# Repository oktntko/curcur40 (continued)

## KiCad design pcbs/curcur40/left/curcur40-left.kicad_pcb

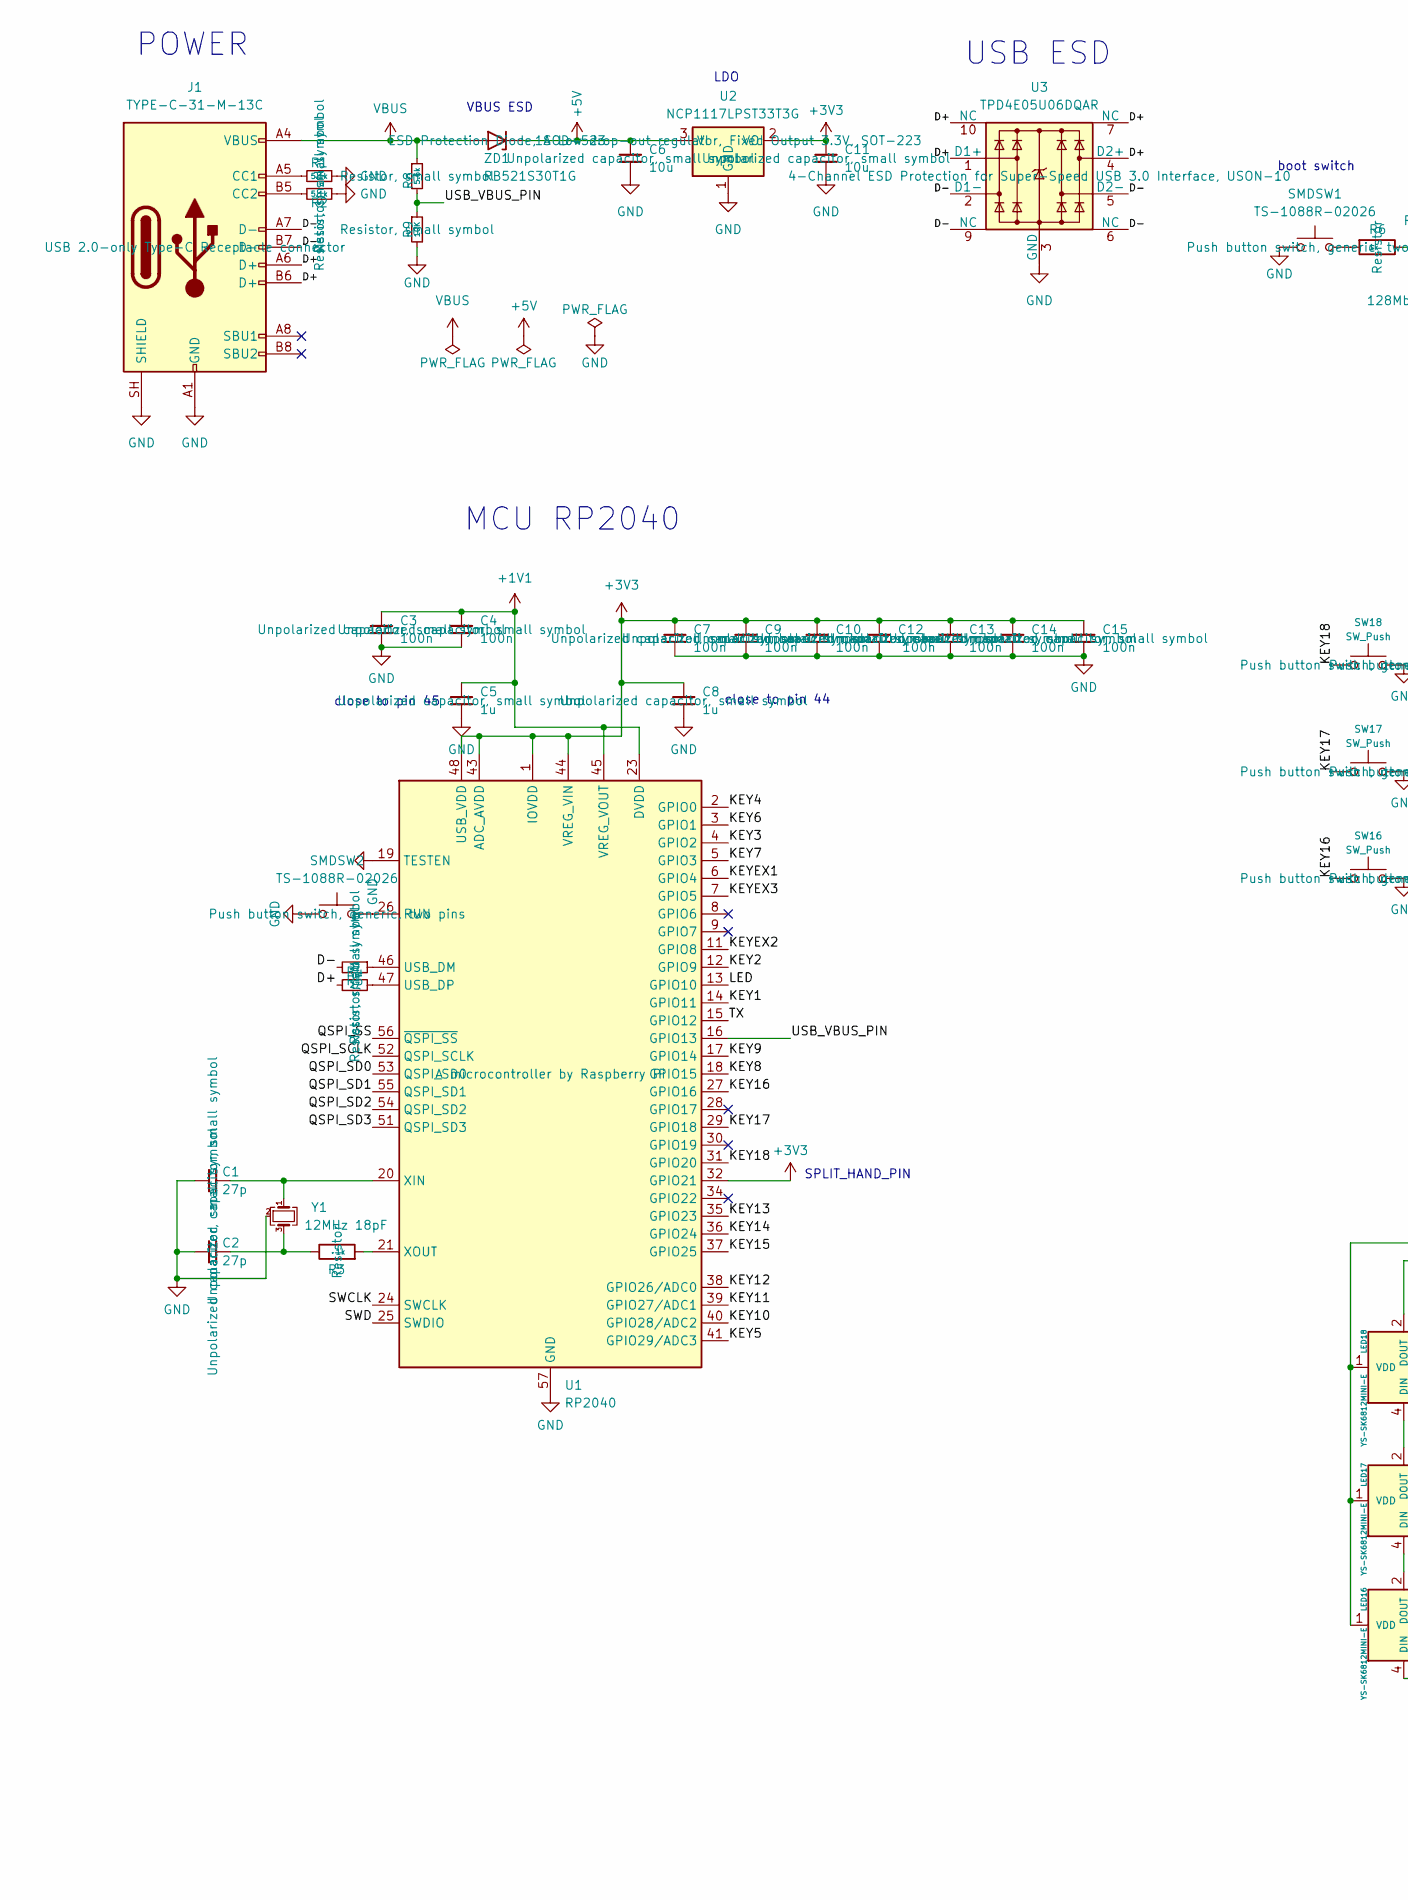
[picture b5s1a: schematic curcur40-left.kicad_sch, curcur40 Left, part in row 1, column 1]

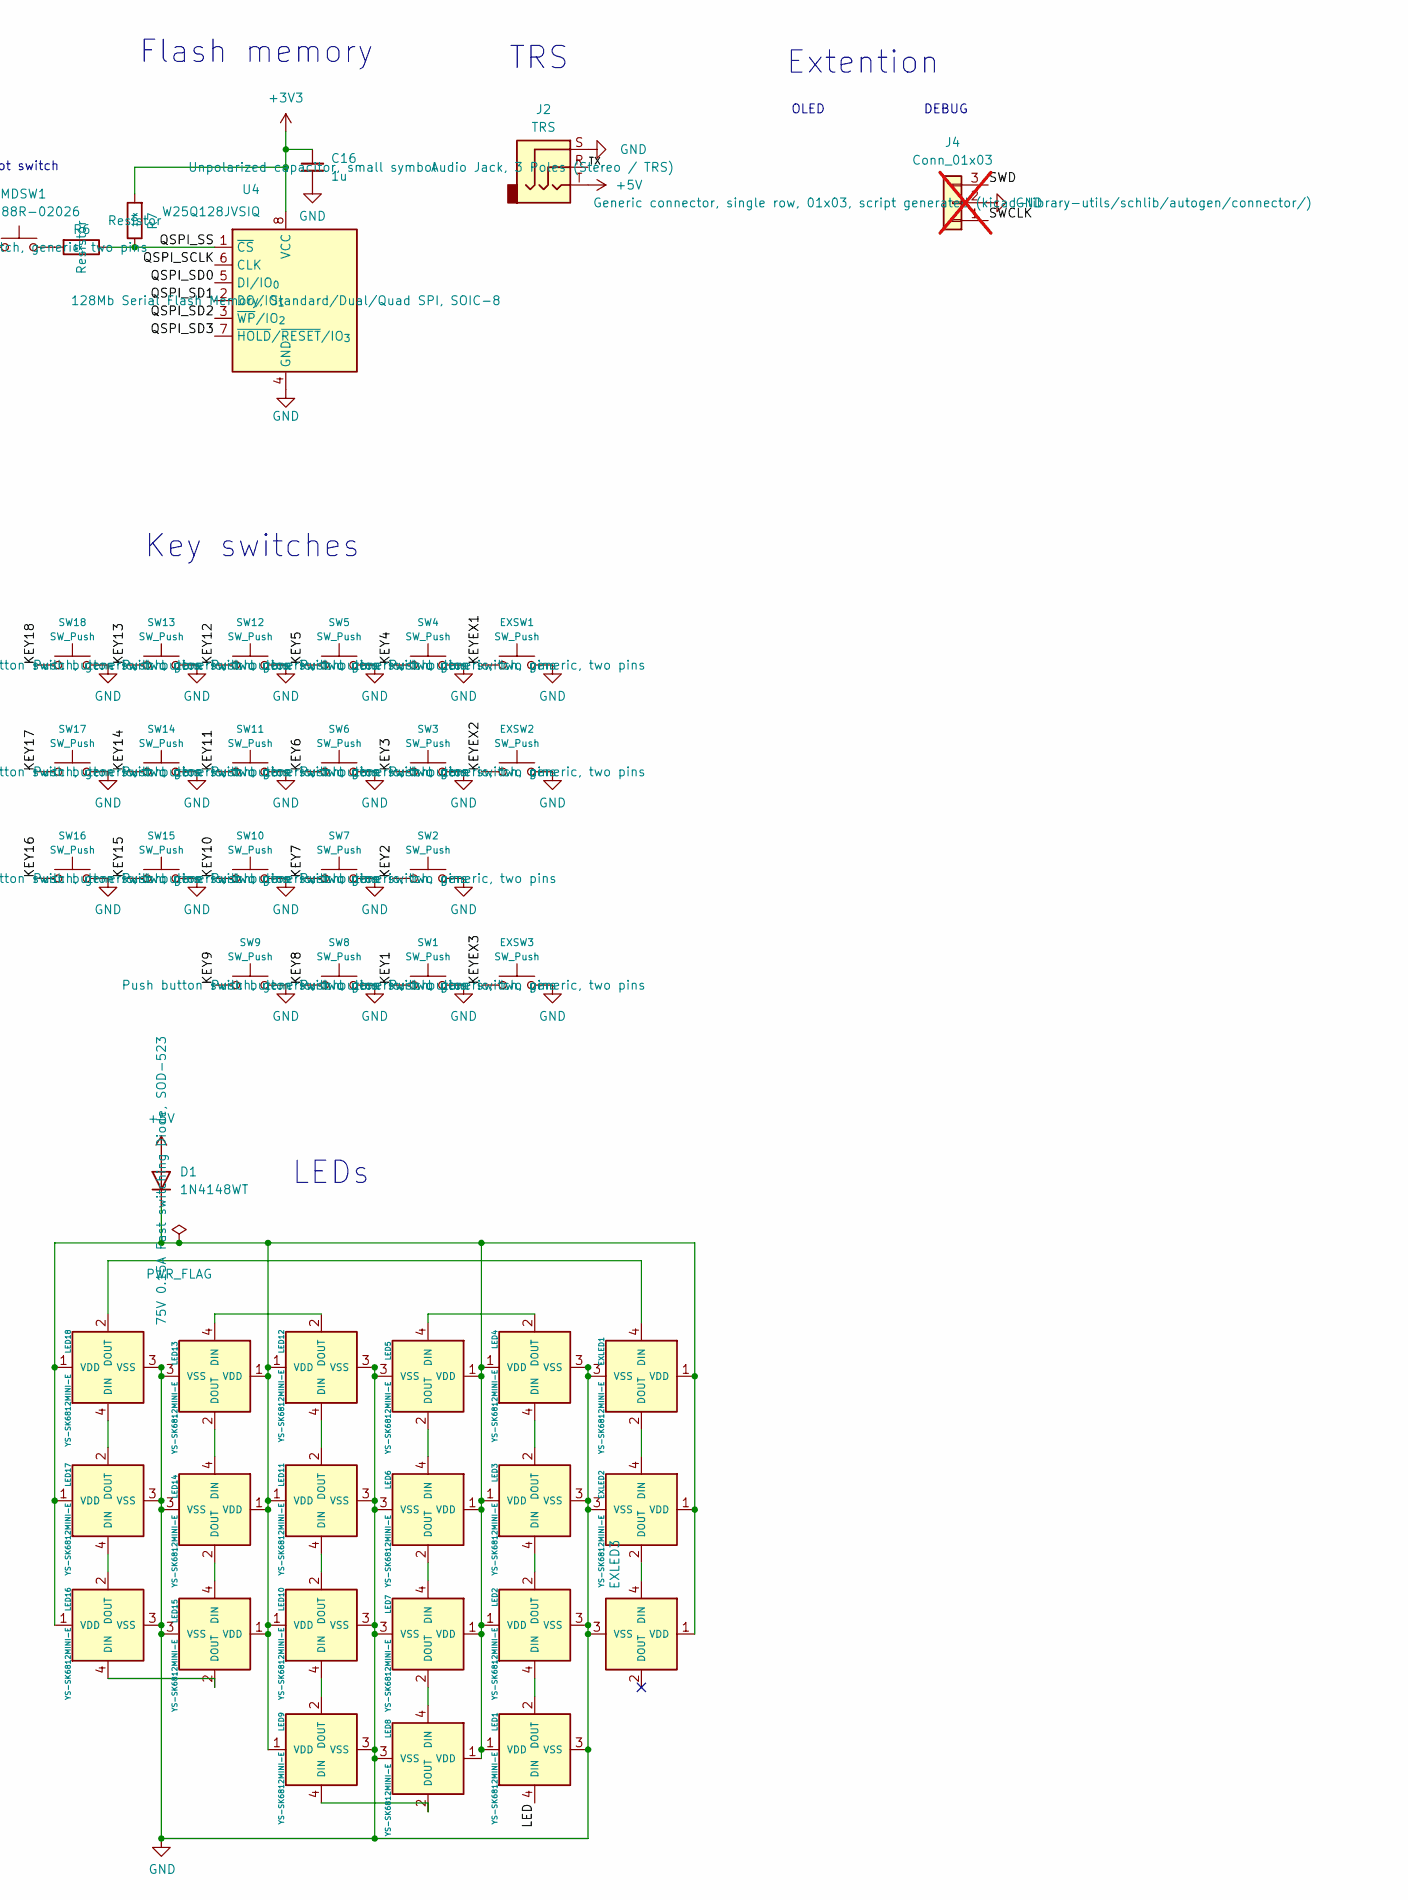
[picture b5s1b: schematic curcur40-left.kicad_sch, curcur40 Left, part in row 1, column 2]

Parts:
C1, C2: 27p; C_0402_1005Metric
C3, C4, C7, C9, C10, C12, C13, C14, C15: 100n; C_0402_1005Metric
C5, C8, C16: 1u; C_0402_1005Metric
C6, C11: 10u; C_0402_1005Metric
D1: 1N4148WT; D_SOD-523; JLCPCB Part # C232841
EXLED1, EXLED2, EXLED3: YS-SK6812MINI-E
EXSW1, EXSW2, EXSW3: SW_Push; keyswitch_choc12_hotswap_1u
J1: TYPE-C-31-M-13C; USB_C_Receptacle_TYPE-C-31-M-13C; JLCPCB Part # C2848620
J2: TRS; Jack_PJ-398A-5A_PJ-399B-6A; JLCPCB Part # C128994
J4: Conn_01x03; PinHeader_1x03_P2.54mm_Vertical; not fitted
LED1, LED2, LED3, LED4, LED5, LED6, LED7, LED8, LED9, LED10, LED11, LED12, LED13, LED14, LED15, LED16, LED17, LED18: YS-SK6812MINI-E
R1, R2: 5.1k; R_0402_1005Metric
R3, R6: 1k; R_0402_1005Metric
R4, R5: 27; R_0402_1005Metric
R7: 10k; R_0402_1005Metric
R8: 5.6k; R_0402_1005Metric
R9: 10K; R_0402_1005Metric
SMDSW1, SMDSW2: TS-1088R-02026; JLCPCB Part # C455280
SW1, SW2, SW3, SW4, SW5, SW6, SW7, SW8, SW9, SW10, SW11, SW12, SW13, SW14, SW15, SW16, SW17, SW18: SW_Push; keyswitch_choc12_hotswap_1u
U1: RP2040; QFN-56-1EP_7x7mm_P0.4mm_EP3.2x3.2mm; JLCPCB Part # C2040
U2: NCP1117LPST33T3G; SOT-223-3_TabPin2; JLCPCB Part # C146799
U3: TPD4E05U06DQAR; USON-10_2.5x1.0mm_P0.5mm; JLCPCB Part # C138714
U4: W25Q128JVSIQ; SOIC-8_5.3x5.3mm_P1.27mm; JLCPCB Part # C113767
Y1: 12MHz 18pF; Crystal_SMD_3225-4Pin_3.2x2.5mm; MFR.Part # Q22FA23V0041800; JLCPCB Part # C91749
ZD1: RB521S30T1G; D_SOD-523; JLCPCB Part # C145179

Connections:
+1V1: C3.1, C4.1, C5.1, U1.23 (DVDD), U1.45 (VREG_VOUT), U1.50 (DVDD)
+3V3: C7.1, C8.1, C9.1, C10.1, C11.1, C12.1, C13.1, C14.1, C15.1, C16.1, R7.2, U1.1 (IOVDD), U1.10 (IOVDD), U1.22 (IOVDD), U1.32 (GPIO21), U1.33 (IOVDD), U1.42 (IOVDD), U1.43 (ADC_AVDD), U1.44 (VREG_VIN), U1.48 (USB_VDD), U1.49 (IOVDD), U2.2 (VO), U4.8 (VCC)
+5V: C6.1, D1.2 (A), J2.T, U2.3 (VI), ZD1.1 (K)
/D+: J1.A6 (D+), J1.B6 (D+), R4.1, U3.1 (D1+), U3.4 (D2+), U3.7 (NC), U3.10 (NC)
/D-: J1.A7 (D-), J1.B7 (D-), R5.2, U3.2 (D1-), U3.5 (D2-), U3.6 (NC), U3.9 (NC)
/KEY1: SW1.1, U1.14 (GPIO11)
/KEY2: SW2.1, U1.12 (GPIO9)
/KEY3: SW3.1, U1.4 (GPIO2)
/KEY4: SW4.1, U1.2 (GPIO0)
/KEY5: SW5.1, U1.41 (GPIO29/ADC3)
/KEY6: SW6.1, U1.3 (GPIO1)
/KEY7: SW7.1, U1.5 (GPIO3)
/KEY8: SW8.1, U1.18 (GPIO15)
/KEY9: SW9.1, U1.17 (GPIO14)
/KEY10: SW10.1, U1.40 (GPIO28/ADC2)
/KEY11: SW11.1, U1.39 (GPIO27/ADC1)
/KEY12: SW12.1, U1.38 (GPIO26/ADC0)
/KEY13: SW13.1, U1.35 (GPIO23)
/KEY14: SW14.1, U1.36 (GPIO24)
/KEY15: SW15.1, U1.37 (GPIO25)
/KEY16: SW16.1, U1.27 (GPIO16)
/KEY17: SW17.1, U1.29 (GPIO18)
/KEY18: SW18.1, U1.31 (GPIO20)
/KEYEX1: EXSW1.1, U1.6 (GPIO4)
/KEYEX2: EXSW2.1, U1.11 (GPIO8)
/KEYEX3: EXSW3.1, U1.7 (GPIO5)
/LED: LED1.4 (DIN), U1.13 (GPIO10)
/QSPI_SCLK: U1.52 (QSPI_SCLK), U4.6 (CLK)
/QSPI_SD0: U1.53 (QSPI_SD0), U4.5 (DI/IO_{0})
/QSPI_SD1: U1.55 (QSPI_SD1), U4.2 (DO/IO_{1})
/QSPI_SD2: U1.54 (QSPI_SD2), U4.3 (~WP/IO_{2})
/QSPI_SD3: U1.51 (QSPI_SD3), U4.7 (~HOLD/~RESET/IO_{3})
/QSPI_SS: R6.1, R7.1, U1.56 (~QSPI_SS), U4.1 (~CS)
/SWCLK: J4.1, U1.24 (SWCLK)
/SWD: J4.3, U1.25 (SWDIO)
/TX: J2.R, U1.15 (GPIO12)
/USB_VBUS_PIN: R8.2, R9.1, U1.16 (GPIO13)
GND: C1.2, C2.2, C3.2, C4.2, C5.2, C6.2, C7.2, C8.2, C9.2, C10.2, C11.2, C12.2, C13.2, C14.2, C15.2, C16.2, EXLED1.3 (VSS), EXLED2.3 (VSS), EXLED3.3 (VSS), EXSW1.2, EXSW2.2, EXSW3.2, J1.A1 (GND), J1.A12 (GND), J1.B1 (GND), J1.B12 (GND), J1.SH (SHIELD), J2.S, J4.2, LED1.3 (VSS), LED2.3 (VSS), LED3.3 (VSS), LED4.3 (VSS), LED5.3 (VSS), LED6.3 (VSS), LED7.3 (VSS), LED8.3 (VSS), LED9.3 (VSS), LED10.3 (VSS), LED11.3 (VSS), LED12.3 (VSS), LED13.3 (VSS), LED14.3 (VSS), LED15.3 (VSS), LED16.3 (VSS), LED17.3 (VSS), LED18.3 (VSS), R1.1, R2.1, R9.2, SMDSW1.1, SMDSW2.1, SW1.2, SW2.2, SW3.2, SW4.2, SW5.2, SW6.2, SW7.2, SW8.2, SW9.2, SW10.2, SW11.2, SW12.2, SW13.2, SW14.2, SW15.2, SW16.2, SW17.2, SW18.2, U1.19 (TESTEN), U1.57 (GND), U2.1 (GND), U3.3 (GND), U3.8 (GND), U4.4 (GND), Y1.2 (G), Y1.4 (G)
unnamed: C2.1, R3.1, Y1.3
unnamed: D1.1 (K), EXLED1.1 (VDD), EXLED2.1 (VDD), EXLED3.1 (VDD), LED1.1 (VDD), LED2.1 (VDD), LED3.1 (VDD), LED4.1 (VDD), LED5.1 (VDD), LED6.1 (VDD), LED7.1 (VDD), LED8.1 (VDD), LED9.1 (VDD), LED10.1 (VDD), LED11.1 (VDD), LED12.1 (VDD), LED13.1 (VDD), LED14.1 (VDD), LED15.1 (VDD), LED16.1 (VDD), LED17.1 (VDD), LED18.1 (VDD)
unnamed: EXLED1.4 (DIN), LED18.2 (DOUT)
unnamed: EXLED1.2 (DOUT), EXLED2.4 (DIN)
unnamed: EXLED2.2 (DOUT), EXLED3.4 (DIN)
unnamed: J1.A5 (CC1), R1.2
unnamed: J1.B5 (CC2), R2.2
unnamed: LED1.2 (DOUT), LED2.4 (DIN)
unnamed: LED2.2 (DOUT), LED3.4 (DIN)
unnamed: LED3.2 (DOUT), LED4.4 (DIN)
unnamed: LED4.2 (DOUT), LED5.4 (DIN)
unnamed: LED5.2 (DOUT), LED6.4 (DIN)
unnamed: LED6.2 (DOUT), LED7.4 (DIN)
unnamed: LED7.2 (DOUT), LED8.4 (DIN)
unnamed: LED8.2 (DOUT), LED9.4 (DIN)
unnamed: LED9.2 (DOUT), LED10.4 (DIN)
unnamed: LED10.2 (DOUT), LED11.4 (DIN)
unnamed: LED11.2 (DOUT), LED12.4 (DIN)
unnamed: LED12.2 (DOUT), LED13.4 (DIN)
unnamed: LED13.2 (DOUT), LED14.4 (DIN)
unnamed: LED14.2 (DOUT), LED15.4 (DIN)
unnamed: LED15.2 (DOUT), LED16.4 (DIN)
unnamed: LED16.2 (DOUT), LED17.4 (DIN)
unnamed: LED17.2 (DOUT), LED18.4 (DIN)
unnamed: R6.2, SMDSW1.2
unnamed: SMDSW2.2, U1.26 (RUN)
unnamed: R5.1, U1.46 (USB_DM)
unnamed: R4.2, U1.47 (USB_DP)
unnamed: C1.1, U1.20 (XIN), Y1.1
unnamed: R3.2, U1.21 (XOUT)
VBUS: J1.A4 (VBUS), J1.A9 (VBUS), J1.B4 (VBUS), J1.B9 (VBUS), R8.1, ZD1.2 (A)

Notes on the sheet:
MCU RP2040
Key switches
OLED
close to pin 45
DEBUG
USB ESD
LDO
Flash memory
POWER
LEDs
Extention
TRS
VBUS ESD
SPLIT_HAND_PIN
boot switch
close to pin 44

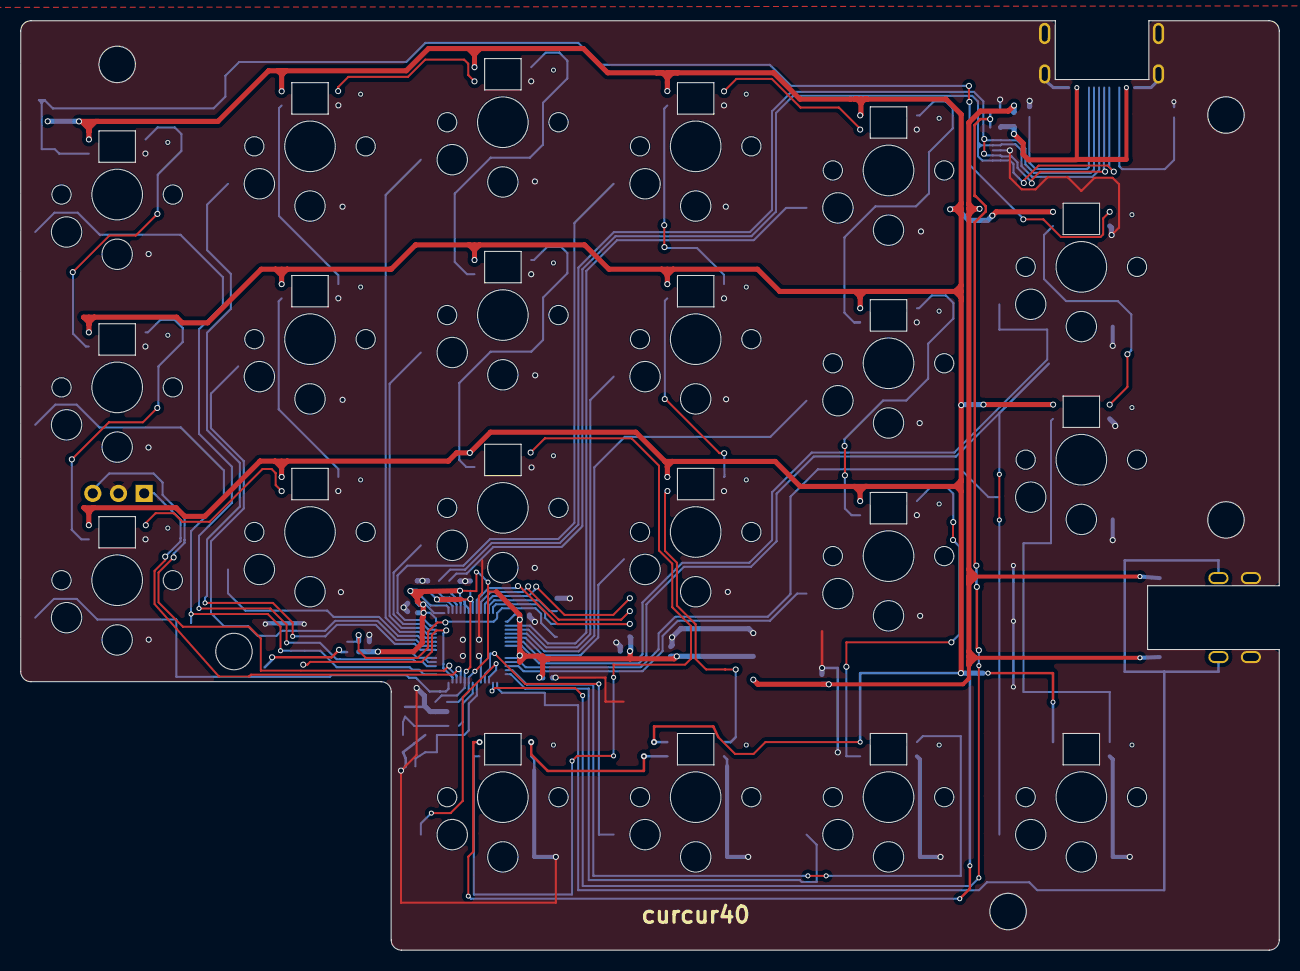
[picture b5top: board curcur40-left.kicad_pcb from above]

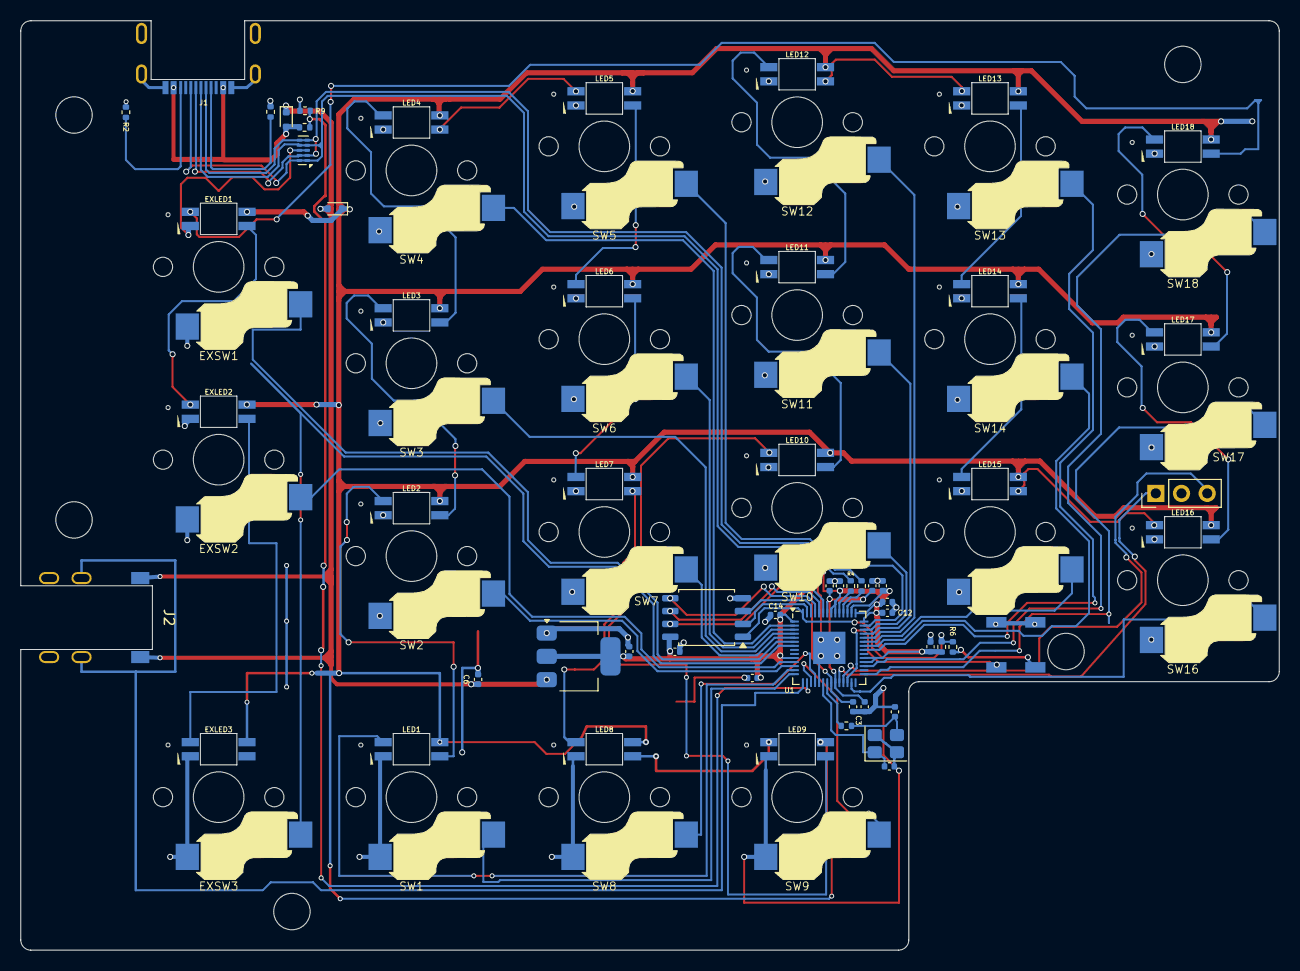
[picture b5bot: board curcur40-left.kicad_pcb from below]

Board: 2 copper layers, 124.3 x 91.8 mm, 79 parts (79 on the bottom side), 69 nets.

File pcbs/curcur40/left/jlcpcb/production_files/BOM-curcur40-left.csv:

Comment,Designator,Footprint,LCSC
W25Q128JVSIQ,U4,SOIC-8_5.3x5.3mm_P1.27mm,C113767
1k,"R3,R6",R_0402_1005Metric,C11702
TRS,J2,PJ-398A-5A_PJ-399B-6A,C128994
TPD4E05U06DQAR,U3,USON-10_2.5x1.0mm_P0.5mm,C138714
RB521S30T1G,ZD1,D_SOD-523,C145179
NCP1117LPST33T3G,U2,SOT-223-3_TabPin2,C146799
100n,"C10,C12,C13,C14,C15,C3,C4,C7,C9",C_0402_1005Metric,C1525
10u,"C11,C6",C_0402_1005Metric,C15525
27p,"C1,C2",C_0402_1005Metric,C1557
RP2040,U1,QFN-56-1EP_7x7mm_P0.4mm_EP3.2x3.2mm,C2040
1N4148WT,D1,D_SOD-523,C232841
10k,"R7,R9",R_0402_1005Metric,C25744
5.1k,"R1,R2",R_0402_1005Metric,C25905
5.6k,R8,R_0402_1005Metric,C25908
TYPE-C-31-M-13C,J1,TYPE-C-31-M-13C,C2848620
27,"R4,R5",R_0402_1005Metric,C2909343
TS-1088R-02026,"SMDSW1,SMDSW2",TS-1088R-02026,C455280
YS-SK6812MINI-E,"EXLED1,EXLED2,EXLED3,LED1,LED10,LED11,LED12,LED13,LED14,LED15,LED16,LED17,LED18,LED2,LED3,LED4,LED5,LED6,LED7,LED8,LED9",YS-SK6812MINI-E,C5149201
1u,"C16,C5,C8",C_0402_1005Metric,C52923
SW_Push,"EXSW1,EXSW2,EXSW3,SW1,SW10,SW11,SW12,SW13,SW14,SW15,SW16,SW17,SW18,SW2,SW3,SW4,SW5,SW6,SW7,SW8,SW9",keyswitch_choc12_hotswap_1u,C5333465
12MHz 18pF,Y1,Crystal_SMD_3225-4Pin_3.2x2.5mm,C91749

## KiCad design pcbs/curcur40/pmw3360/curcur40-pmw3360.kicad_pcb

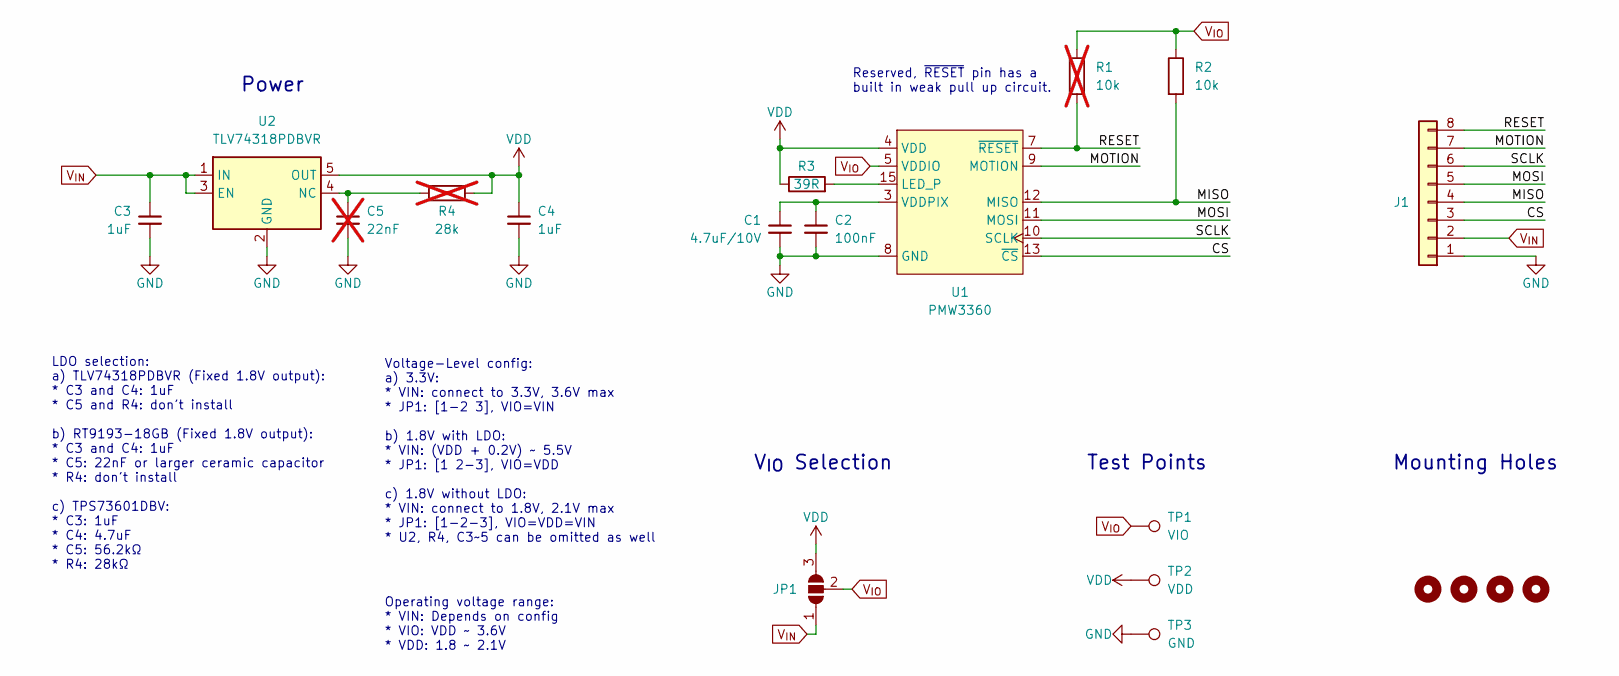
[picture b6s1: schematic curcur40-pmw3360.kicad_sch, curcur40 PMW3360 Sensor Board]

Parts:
C1: 4.7uF/10V; C_0603_1608Metric_Pad1.08x0.95mm_HandSolder; Mfr. # CL10A475KO8NNNC; LCSC C19666
C2: 100nF; C_0603_1608Metric_Pad1.08x0.95mm_HandSolder; Mfr. # CC0603KRX7R9BB104; LCSC C14663
C3, C4: 1uF; C_0603_1608Metric_Pad1.08x0.95mm_HandSolder; Mfr. # CL10A105KB8NNNC; LCSC C15849
C5: 22nF; C_0603_1608Metric_Pad1.08x0.95mm_HandSolder; Mfr. # CL10B223KB8NNNC; LCSC C21122; not fitted
H1, H2, H3, H4: MountingHole_2.2mm_M2
J1: Conn_01x08; PinHeader_1x08_P2.54mm_Vertical
JP1: SolderJumper_3_Open; SolderJumper-3_P1.3mm_Open_RoundedPad1.0x1.5mm_NumberLabels
R1: 10k; R_0603_1608Metric_Pad0.98x0.95mm_HandSolder; Mfr. # 0603WAF1002T5E; LCSC C25804; not fitted
R2: 10k; R_0603_1608Metric_Pad0.98x0.95mm_HandSolder; Mfr. # 0603WAF1002T5E; LCSC C25804
R3: 39R; R_0603_1608Metric_Pad0.98x0.95mm_HandSolder; Mfr. # 0603WAF390JT5E; LCSC C23154
R4: 28k; R_0603_1608Metric_Pad0.98x0.95mm_HandSolder; not fitted
TP1: VIO; TestPoint_Pad_D1.5mm
TP2: VDD; TestPoint_Pad_D1.5mm
TP3: GND; TestPoint_Pad_D1.5mm
U1: PMW3360; PMW3360DM-T2QU_16Pin; Mfr. # PMW3360DM-T2QU + LM19-LSI
U2: TLV74318PDBVR; SOT-23-5; Mfr. # TLV74318PDBVR; LCSC C485152

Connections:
/CS: J1.3, U1.13 (~CS)
/MISO: J1.4, R2.2, U1.12 (MISO)
/MOSI: J1.5, U1.11 (MOSI)
/MOTION: J1.7, U1.9 (MOTION)
/RESET: J1.8, R1.2, U1.7 (~RESET)
/SCLK: J1.6, U1.10 (SCLK)
GND: C1.2, C2.2, C3.2, C4.2, C5.2, J1.1, TP3.1, U1.8 (GND), U2.2 (GND)
unnamed: R3.2, U1.15 (LED_P)
unnamed: C1.1, C2.1, U1.3 (VDDPIX)
unnamed: C5.1, R4.2, U2.4 (NC)
VDD: C4.1, JP1.3 (B), R3.1, R4.1, TP2.1, U1.4 (VDD), U2.5 (OUT)
V_{IN}: C3.1, J1.2, JP1.1 (A), U2.1 (IN), U2.3 (EN)
V_{IO}: JP1.2 (C), R1.1, R2.1, TP1.1, U1.5 (VDDIO)

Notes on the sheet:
Voltage-Level config: a) 3.3V: * VIN: connect to 3.3V, 3.6V max * JP1: [1-2 3], VIO=VIN b) 1.8V with LDO: * VIN: (VDD + 0.2V) ~ 5.5V * JP1: [1 2-3], VIO=VDD c) 1.8V without LDO: * VIN: connect to 1.8V, 2.1V max * JP1: [1-2-3], VIO=VDD=VIN * U2, R4, C3~5 can be omitted as well
Operating voltage range: * VIN: Depends on config * VIO: VDD ~ 3.6V * VDD: 1.8 ~ 2.1V
V_{IO} Selection
LDO selection: a) TLV74318PDBVR (Fixed 1.8V output): * C3 and C4: 1uF * C5 and R4: don't install b) RT9193-18GB (Fixed 1.8V output): * C3 and C4: 1uF * C5: 22nF or larger ceramic capacitor * R4: don't install c) TPS73601DBV: * C3: 1uF * C4: 4.7uF * C5: 56.2kΩ * R4: 28kΩ
Reserved, ~{RESET} pin has a built in weak pull up circuit.
Test Points
Mounting Holes
Power

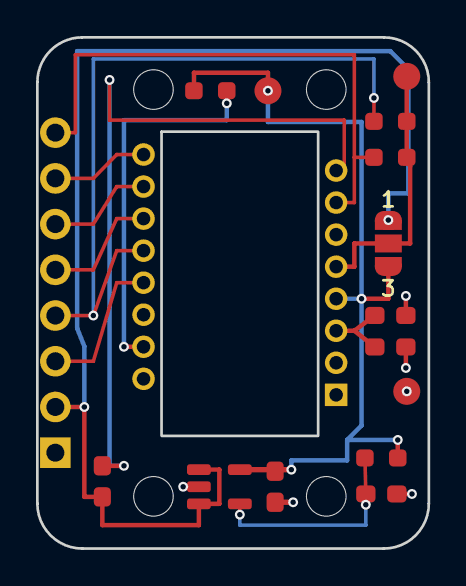
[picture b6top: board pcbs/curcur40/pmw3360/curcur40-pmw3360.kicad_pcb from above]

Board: 2 copper layers, 21.8 x 28.4 mm, 20 parts (0 on the bottom side), 13 nets.
